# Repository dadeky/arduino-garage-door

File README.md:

# arduino-garage-door
C++ Arduino application that manages opening the garage doors

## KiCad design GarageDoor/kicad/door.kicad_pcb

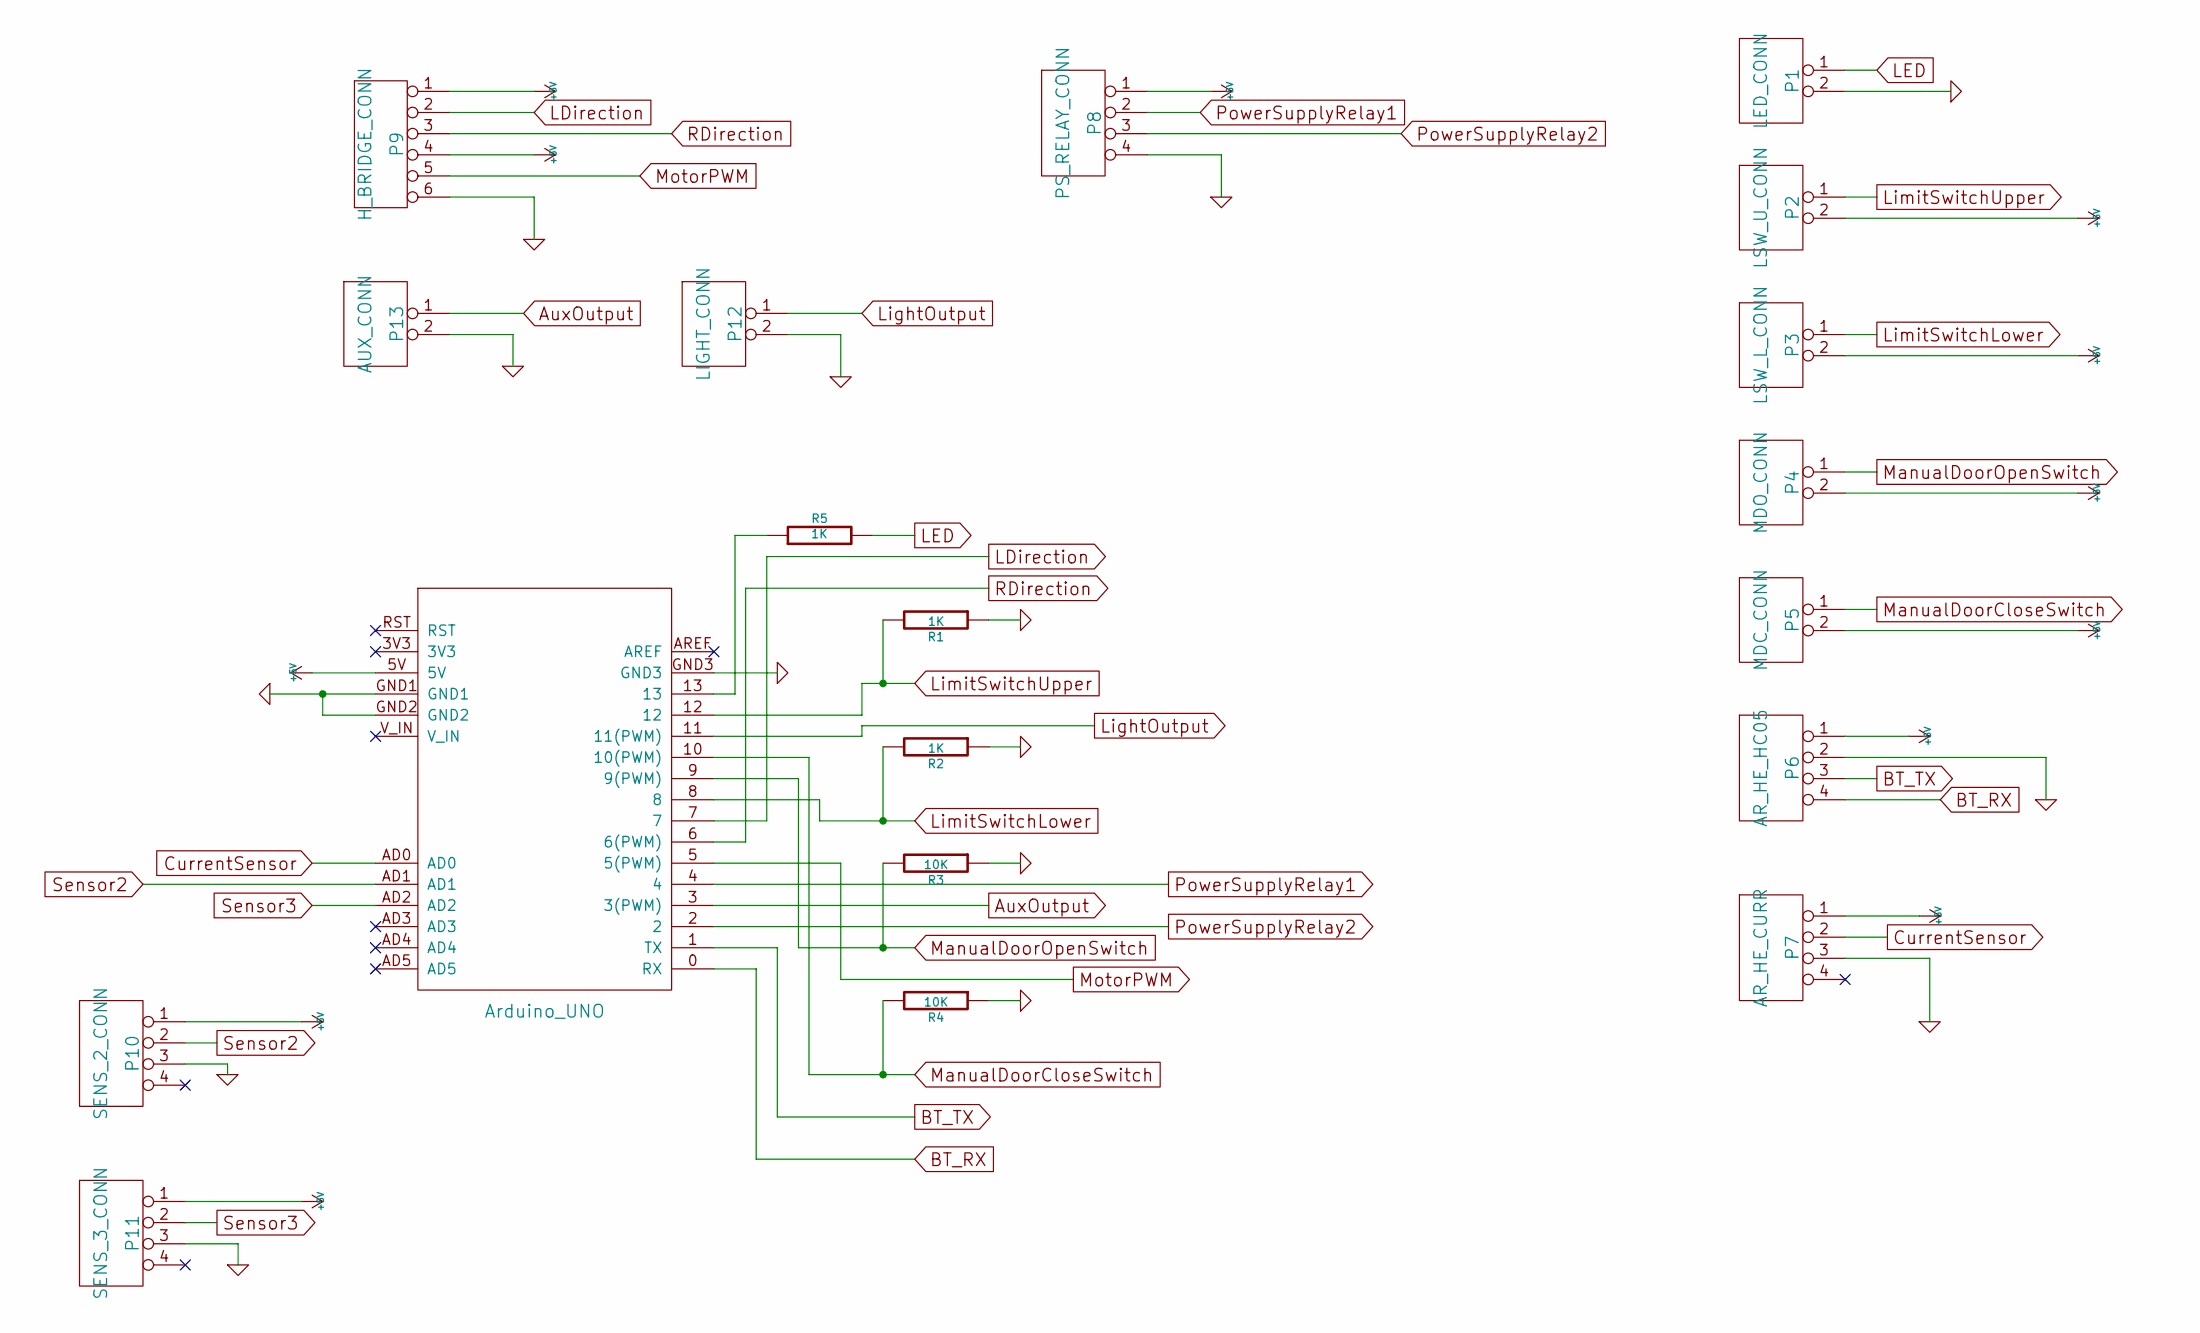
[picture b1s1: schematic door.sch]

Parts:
P1: LED_CONN; AK300-2
P2: LSW_U_CONN; AK300-2
P3: LSW_L_CONN; AK300-2
P4: MDO_CONN; AK300-2
P5: MDC_CONN; AK300-2
P6: AR_HE_HC05; Socket_Strip_Straight_1x04
P7: AR_HE_CURR; Socket_Strip_Straight_1x04
P8: PS_RELAY_CONN; AK300-4
P9: H_BRIDGE_CONN; CONN_6
P10: SENS_2_CONN; AK300-4
P11: SENS_3_CONN; AK300-4
P12: LIGHT_CONN; AK300-2
P13: AUX_CONN; AK300-2
R1, R2, R5: 1K; R3-LARGE_PADS
R3, R4: 10K; R3-LARGE_PADS
UNO1: Arduino_UNO; ARDUINO_UNO_SHIELD

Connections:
+5V: P2.2, P3.2, P4.2, P5.2, P6.1, P7.1, P8.1, P9.1, P9.4, P10.1, P11.1, UNO1.5V
AuxOutput: P13.1, UNO1.3 (3(PWM))
BT_RX: P6.4, UNO1.0 (RX)
BT_TX: P6.3, UNO1.1 (TX)
CurrentSensor: P7.2, UNO1.AD0
GND: P1.2, P6.2, P7.3, P8.4, P9.6, P10.3, P11.3, P12.2, P13.2, R1.1, R2.1, R3.1, R4.1, UNO1.GND1, UNO1.GND2, UNO1.GND3
LDirection: P9.2, UNO1.7
LED: P1.1, R5.2
LightOutput: P12.1, UNO1.11 (11(PWM))
LimitSwitchLower: P3.1, R2.2, UNO1.8
LimitSwitchUpper: P2.1, R1.2, UNO1.12
ManualDoorCloseSwitch: P5.1, R4.2, UNO1.10 (10(PWM))
ManualDoorOpenSwitch: P4.1, R3.2, UNO1.9 (9(PWM))
MotorPWM: P9.5, UNO1.5 (5(PWM))
unnamed: R5.1, UNO1.13
PowerSupplyRelay1: P8.2, UNO1.4
PowerSupplyRelay2: P8.3, UNO1.2
RDirection: P9.3, UNO1.6 (6(PWM))
Sensor2: P10.2, UNO1.AD1
Sensor3: P11.2, UNO1.AD2

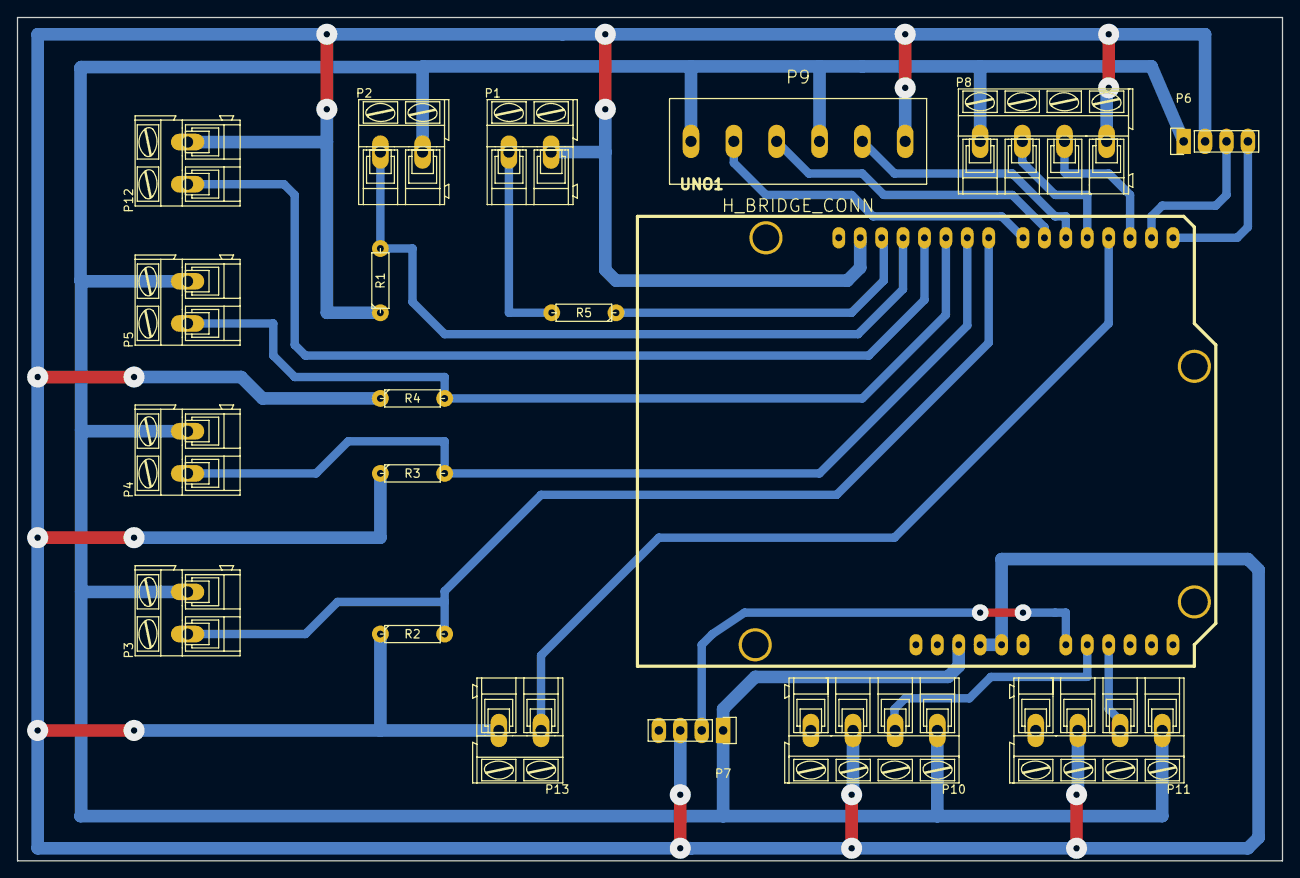
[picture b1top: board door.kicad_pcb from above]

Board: 2 copper layers, 150.0 x 100.0 mm, 19 parts (0 on the bottom side), 20 nets.

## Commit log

2015-07-27 Post initial commit
2015-07-27 Project files
2015-08-18 lang
2015-10-02 Bounce2 lib added.
2015-10-02 Setting the initial value to low.
2015-10-02 Internal pull-up's added.
2015-10-03 Pull-down changed to 4,7 kohm
2015-10-05 Test.
2015-10-06 Improvements.
2015-10-07 Return back to reading the upperLimitSwitch.
2015-10-07 Ignore
2015-10-07 Some more changes.
2015-10-08 Testing the behavior of upper limit switch.
2015-10-09 Kicad
2015-10-09 KiCad.
2015-10-10 Kicad stuff.
2016-06-08 Compiled with new V3 Arduino plugin
2016-08-19 Enabled lower limit switch
2016-08-19 Slow start duration decreased
2016-08-19 Compiled
2016-08-19 delay changed
2017-12-28 new sloeber version
2018-01-08 One too many include.
2018-01-26 Date
2018-03-14 Some fixes
2018-03-15 Door state indicator sent now
2018-05-31 door state indicator added
2018-06-01 new release
2018-06-22 Some
2018-07-12 Photon
2024-09-15 maxCurrentDown changed to 650
